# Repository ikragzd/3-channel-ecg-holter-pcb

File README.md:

# Portable 3-Channel ECG Holter Monitor PCB

A compact, 4-layer custom printed circuit board designed for continuous 24+ hour, 3-channel electrocardiogram data logging to a microSD card with on-demand Bluetooth Low Energy transfer.

> **Disclaimer:** This hardware is an open-source personal monitoring and engineering prototype. It is not a certified medical device and is not intended for clinical diagnosis. For electrical safety, ECG electrodes must be disconnected whenever the device is connected to USB for charging.

## Hardware Architecture
* **Analog Front-End:** Texas Instruments **ADS1293** 3-channel, 24-bit resolution biopotential AFE with hardware lead-off detection
* **Main Processor:** **ESP32 WROOM-32** module managing SPI communication, time-stamping, and user-triggered BLE transfer
* **Data Storage:** SPI **microSD** card slot with card-detect support for continuous raw waveform logging at 250 Hz or higher per channel
* **Real-Time Clock:** External **DS3231** class RTC ensuring accurate timestamps across battery cycles
* **Power & Charging:** **TP4056** protected LiPo battery charger, JST-PH 2.0 connector for 1000–2000mAh LiPo cells, reverse-polarity protection diode, and resistive voltage divider for low-battery monitoring
* **Programming Interface:** Onboard **CP2102 / CH340** USB-to-UART bridge for firmware flashing and serial debugging
* **Input Protection:** TVS ESD protection diodes and series current-limiting safety resistors across 4 to 5 ECG electrode inputs including RLD

## PCB Layout & Engineering Specifications
* **4-Layer Stackup & Star Grounding:** Dedicated analog and digital ground planes joined at a single star-ground point to prevent high-frequency noise from coupling into low-amplitude ECG traces.
* **RF & Analog Isolation:** Short, guarded analog traces near the electrode connector, with physical separation and a copper keep-out zone beneath the ESP32 internal antenna.
* **Mechanical & Reliability Targets:** Designed under 50 g total weight and 10 mm PCB thickness, featuring mounting holes, electrode cable strain relief, SPI/power test points, and conformal-coating compatibility targeting IP54 moisture resistance.

## Attribution
Derived from the open-source **ProtoCentral ADS1293 3-Channel ECG Breakout** hardware reference, licensed under Creative Commons Attribution-ShareAlike.

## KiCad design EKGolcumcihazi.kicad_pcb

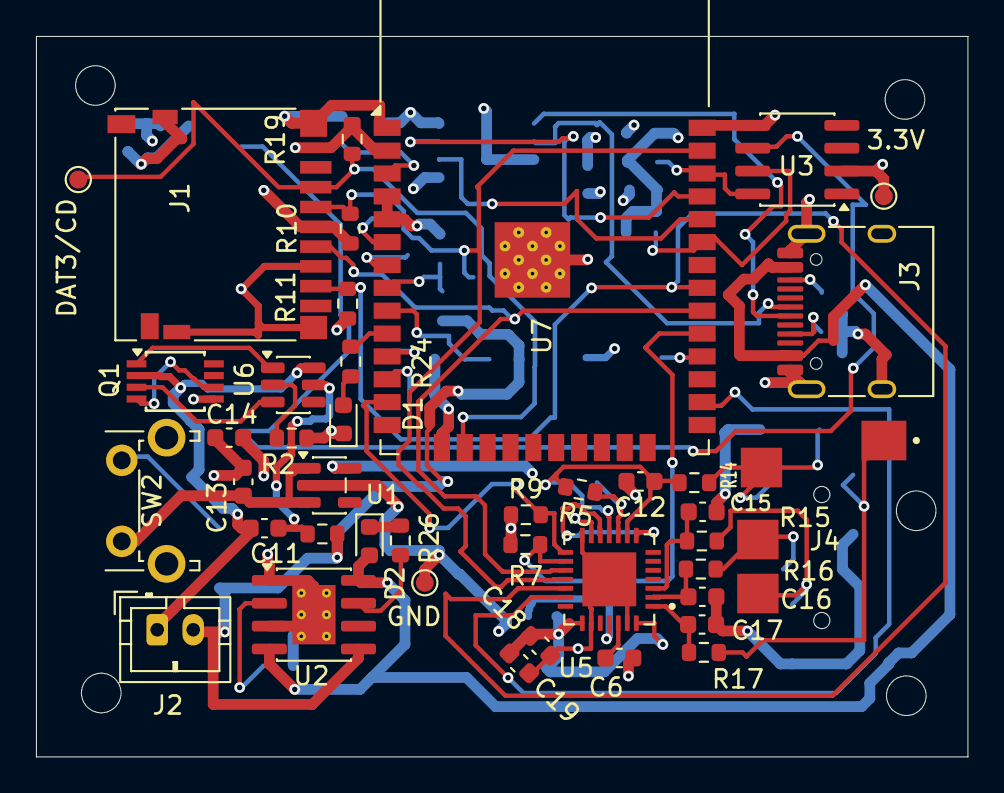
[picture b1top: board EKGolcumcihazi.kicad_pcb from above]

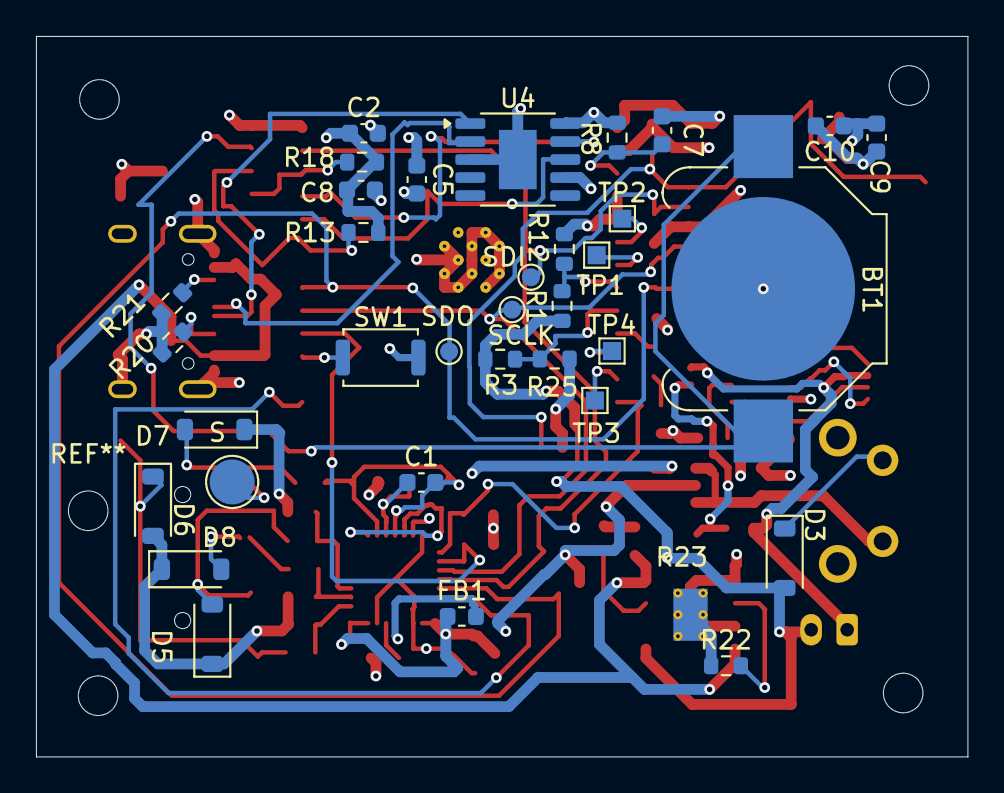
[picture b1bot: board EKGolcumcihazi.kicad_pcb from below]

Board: 4 copper layers, 51.8 x 40.0 mm, 75 parts (34 on the bottom side), 53 nets.

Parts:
3.3V: TestPoint_Pad_D1.0mm
BT1: CR2032; BatteryHolder_Keystone_3000_1x12mm
C1: 1.5nF; C_0603_1608Metric
C2, C8, C9, C11, C18: 100nF; C_0603_1608Metric
C5, C10, C19: 10uF; C_0603_1608Metric
C6: 2.2uF; C_0603_1608Metric
C7, C13, C14: 1uF; C_0603_1608Metric
C12, C15, C16, C17: 1nF; C_0603_1608Metric
D1, D2: LED; LED_0603_1608Metric
D3: D_Schottky_Small; D_SOD-123
D5, D6, D7, D8: D_TVS_Small; D_SOD-123
DAT3/CD: TestPoint_Pad_D1.0mm
FB1: FerriteBead_Small; L_0603_1608Metric
GND: TestPoint_Pad_D1.0mm
J1: Micro_SD_Card; microSD_HC_Hirose_DM3D-SF
J2: PİL SOKET; JST_PH_B2B-PH-K_1x02_P2.00mm_Vertical
J3: USB_C_Receptacle_USB2.0_16P; USB_C_Receptacle_HRO_TYPE-C-31-M-12
J4: AudioJack4; SAMESKY_SJ2-3574A-SMT-TR
Q1: Q_Dual_NMOS; TSSOP-8_3x3mm_P0.65mm
R1, R12: 100k; R_0603_1608Metric
R2, R26: 1k; R_0603_1608Metric
R3, R7, R8, R9, R10, R11, R19, R25: 10k; R_0603_1608Metric
R5: 1M; R_0603_1608Metric
R13, R18: 4.7k; R_0603_1608Metric
R14, R15, R16, R17: 47k; R_0603_1608Metric
R20, R21: 5.1k; R_0603_1608Metric
R22: 2k; R_0603_1608Metric
R23: 100; R_0603_1608Metric
R24: 330; R_0603_1608Metric
S: TestPoint_Pad_D2.5mm
SCLK: TestPoint_Pad_D1.0mm
SDI: TestPoint_Pad_D1.0mm
SDO: TestPoint_Pad_D1.0mm
SW1: SW_Push; SW_Push_SPST_NO_Alps_SKRK
SW2: AC/KAPA; SW_Tactile_SPST_Angled_PTS645Vx58-2LFS
TP1, TP2, TP3, TP4: TestPoint; TestPoint_Pad_1.0x1.0mm
U1: AP2112K-3.3; SOT-23-5
U2: TP4056-42-ESOP8; SOIC-8-1EP_3.9x4.9mm_P1.27mm_EP2.41x3.3mm_ThermalVias
U3: DS3231MZ; SOIC-8_3.9x4.9mm_P1.27mm
U4: CH340K; SSOP-10-1EP_3.9x4.9mm_P1mm_EP2.1x3.3mm
U5: ADS1293CISQ; QFN50P500X500X80-29N
U6: DW01A; SOT-23-6
U7: ESP32-WROOM-32

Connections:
+3.3V: 3.3V.1, C2.1, C5.1, C8.1, C9.1, C10.1, C14.1, FB1.2, J1.4 (VDD), R7.1, R8.1, R9.1, R10.1, R11.1, R13.2, R18.1, R19.1, U1.5 (VOUT), U3.2 (VCC), U4.7 (VCC), U4.10 (V3), U5.13 (SYNCB), U5.25 (RSTB), U7.2 (VDD)
ALARMB: R9.2, U5.15 (ALARMB), U7.13 (IO14)
B1: SW1.1, U7.28 (IO17)
BAT+: D3.2 (A), J2.2, R1.1, R3.1, R23.2, U2.5 (BAT)
BAT-: C11.2, J2.1, Q1.2 (S), U6.6 (GND)
CSB: R7.2, U5.16 (CSB), U7.29 (IO5)
D+: J3.A6 (D+), U4.1 (UD+)
D-: J3.A7 (D-), U4.2 (UD-)
DAT3/CD: DAT3/CD.1, J1.2 (DAT3/CD), R19.2, U7.16 (IO13)
DRDYB: U5.20 (DRDYB), U7.26 (IO4)
GND: BT1.2 (-), C2.2, C5.2, C6.2, C7.2, C8.2, C9.2, C10.2, C12.2, C13.2, C14.2, C15.2, C16.2, C17.2, C18.2, C19.2, D1.1 (K), D5.1 (A1), D6.2 (A2), D7.1 (A1), D8.1 (A1), GND.1, J1.6 (VSS), J1.SH (SHIELD), J3.A1 (GND), J3.A12 (GND), J3.B1 (GND), J3.B12 (GND), J3.SH (SHIELD), Q1.5 (S), R2.2, R12.2, R20.1, R21.1, R22.1, R25.2, SW1.2, U1.2 (GND), U2.1 (TEMP), U2.3 (GND), U2.9 (EPAD), U3.5 (GND), U4.3 (GND), U4.11 (GND), U5.14 (VSSIO), U5.23 (XTAL1), U5.27 (VSS), U5.29 (DAP), U7.1 (GND), U7.4 (SENSOR_VP), U7.5 (SENSOR_VN), U7.15 (GND), U7.38 (GND), U7.39 (GND)
IN1: C17.1, R17.1, U5.1 (IN1)
IN2: C16.1, R16.1, U5.2 (IN2)
IN3: C15.1, R15.1, U5.3 (IN3)
L1: R24.1, U7.10 (IO25)
unnamed: BT1.1 (+), U3.6 (VBAT)
unnamed: D1.2 (A), R24.2
unnamed: D2.1 (K), R26.1
unnamed: D3.1 (K), SW2.2
unnamed: J3.A5 (CC1), R20.2
unnamed: J3.B5 (CC2), R21.2
unnamed: Q1.4 (D), Q1.6 (D)
unnamed: R22.2, U2.2 (PROG)
unnamed: R26.2, U2.7 (~CHRG)
unnamed: U5.8 (CMOUT), U5.12 (RLDREF)
unnamed: C6.1, U5.26 (CVREF)
unnamed: C1.1, R5.1, U5.10 (RLDINV)
unnamed: C18.1, C19.1, FB1.1, U5.22 (VDDIO), U5.28 (VDD)
unnamed: R2.1, U6.2 (CS)
unnamed: C11.1, R23.1, U6.5 (VCC)
unnamed: C7.1, R8.2, U7.3 (EN)
unnamed: TP4.1 (1_1), U7.11 (IO26)
unnamed: TP3.1 (1_1), U7.12 (IO27)
unnamed: TP2.1 (1_1), U7.6 (IO34)
unnamed: TP1.1 (1_1), U7.7 (IO35)
OC: Q1.3 (G), U6.3 (OC)
OD: Q1.1 (G), U6.1 (OD)
PİL: R1.2, R12.1, U7.8 (IO32)
R1: D8.2 (A2), J4.3, R16.2
R2: D5.2 (A2), J4.4, R15.2
RLDOUT: C1.2, C12.1, R5.2, R14.1, U5.9 (RLDOUT), U5.11 (RLDIN)
RXD: U4.9 (RXD), U7.35 (TXD0/IO1)
S: D7.2 (A2), J4.2, R14.2, S.1
SCL: R18.2, U3.8 (SCL), U7.36 (IO22)
SCLK: J1.5 (CLK), SCLK.1, U5.17 (SCLK), U7.30 (IO18)
SDA: R13.1, U3.7 (SDA), U7.33 (IO21)
SDI: J1.3 (CMD), R10.2, SDI.1, U5.18 (SDI), U7.37 (IO23)
SDO: J1.7 (DAT0), R11.2, SDO.1, U5.19 (SDO), U7.31 (IO19)
T: D6.1 (A1), J4.1, R17.2
TXD: U4.8 (TXD), U7.34 (RXD0/IO3)
USB: R3.2, R25.1, U7.9 (IO33)
VBUS: D2.2 (A), J3.A4 (VBUS), J3.A9 (VBUS), J3.B4 (VBUS), J3.B9 (VBUS), U2.4 (V_{CC}), U2.8 (CE)
VIN: C13.1, SW2.1, U1.1 (VIN), U1.3 (EN)
